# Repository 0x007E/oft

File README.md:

# `OFT` - Optical Fibre Transceiver

The `OFT` project is based on a fibre optic transmitter an receiver ([FB104](#additional-information)). The transmitter is based on a high-output medium-speed infrared LED while the transceiver is built on a high-sensitivity NPN phototransistor. Both are housed in a connector-less style plastic fiber optic package. The transmitter has a typical peak wavelength of `930nm`. The bandwith of the receiver is between `400nm` to `1100nm`. The maximum photosensitivity is around `870nm`. The receiver and transmitter is connected with an `RX` and `TX` LED over a `NE555` timer circuit to indicate if a data transmission occurrs.

> Note that the `IF-D92` is suitable for digital data links at rates up to `20kbps`!

| Experience | Level |
|:------------|:-----:|
| Soldering   |  |
| Mechanical  |  |

# Downloads

| Type      | File               | Description              |
|:---------:|:------------------:|:-------------------------|
| Schematic | [pdf](https://github.com/0x007E/oft/releases/latest/download/schematic.pdf) / [cadlab](https://cadlab.io/project/29648/main/files) | Schematic files |
| Board | [pdf](https://github.com/0x007E/oft/releases/latest/download/pcb.pdf) / [cadlab](https://cadlab.io/project/29648/main/files) | Board file |
| Drill | [pdf](https://github.com/0x007E/oft/releases/latest/download/drill.pdf) | Drill file |
| BoM | [xlsx](https://github.com/0x007E/oft/releases/latest/download/bom.xlsx) / [html](https://github.com/0x007E/oft/releases/latest/download/ibom.html)          | Bill of Material as Excel/interactive HTML |
| PCB    | [zip](https://github.com/0x007E/oft/releases/latest/download/kicad.zip) / [tar](https://github.com/0x007E/oft/releases/latest/download/kicad.tar.gz)    | KiCAD/Gerber/BoM/Drill files       |
| Mechanical | [zip](https://github.com/0x007E/oft/releases/latest/download/freecad.zip) / [tar](https://github.com/0x007E/oft/releases/latest/download/freecad.tar.gz) | FreeCAD/Housing and PCB (STEP/STL) files     |

# Hardware

There are two parts of the hardware. The pcb and the housing of the `OFT`. The pcb is created with [KiCAD](#additional-information) and the housing with `FreeCAD`. All files are built with `github actions` so that they are ready for a production environment. The housing is printed with a 3D-printer (`Dremel 3D40`).

## PCB

The circuit board is populated on both sides (Top, Bottom). The best way for soldering the `SMD` components is within a vapor phase soldering system and for the `THT` components with a standard soldering system.

### Top Layer

### Bottom Layer

## Mechanical

The housing has a tolerance of `0.2mm` on each side of the case. So the pcb should fit perfectly in the housing. The tolerance can be modified with `FreeCAD` in the `Parameter` Spreadsheet.

### Assembled

#### Exploded

# Connection/Setup

The `OFT` is powerd with `5V`. The `RX` pin serves as an output and stores the received data at the output so that it can be read by the device. The `TX` pin servs as an input and sends the received data at the input over the fibre channel. The levels of both pins are `LOW = 0V` and `HIGH = 5V`.

``` bash
#
#                                      +----------------+      +---------------------+
#                                      |    U       +---+---+  |                     |
#                                      |    S       |  USB  |--+ +-----------------+ |
#                                      |    B       +---+---+  | | TeraTerm        | |
#              +-------------+         |    /           |      | | ~~~~~~~~        | |
#              |      O      |         |    U           |      | | ~~~~~           | |
#            +--+--+  F   +--+--+   +--+--+ A           |      | | ~~~~~~~~~~~~    | |
#      L +---+ ORX |  T   | VCC +---+ VCC | R           |      | |                 | |
#      O |   +--+--+      | GND +---+ GND | T  +-+      |      | +-----------------+ |
#      O |      |         +-----+   +-----+   / /       |      |                     |
#      P |   +--+--+      | RXD +---+ RXD | +-+-+-+-----+      | Computer            |
#      B +---+ OTX |      | TXD +---+ TXD | | 5V  | 3V3 |      |                     |
#      A     +--+--+      +--+--+   +--+--+ +-----+-----+      +---------------------+
#      C       |             |
#      K       +-------------+                                            
#
```

> The maximum baudrate should be about `~19200bps`!

# Additional Information

| Type       | Link                                                   | Description                            |
|:----------:|:------------------------------------------------------:|:---------------------------------------|
| IF-E10     | [pdf](https://i-fiberoptics.com/pdf/if-e10.pdf)        | Optical fibre receiver and transmitter |
| NE555      | [pdf](https://www.ti.com/lit/ds/symlink/se555.pdf)     | Universal timer and oscillator         |
| KiCAD      | [web](https://www.kicad.org/)                          | KiCAD project page                     |
| FreeCAD    | [web](https://www.freecad.org/)                        | FreeCAD project page                   |

---

R. GAECHTER

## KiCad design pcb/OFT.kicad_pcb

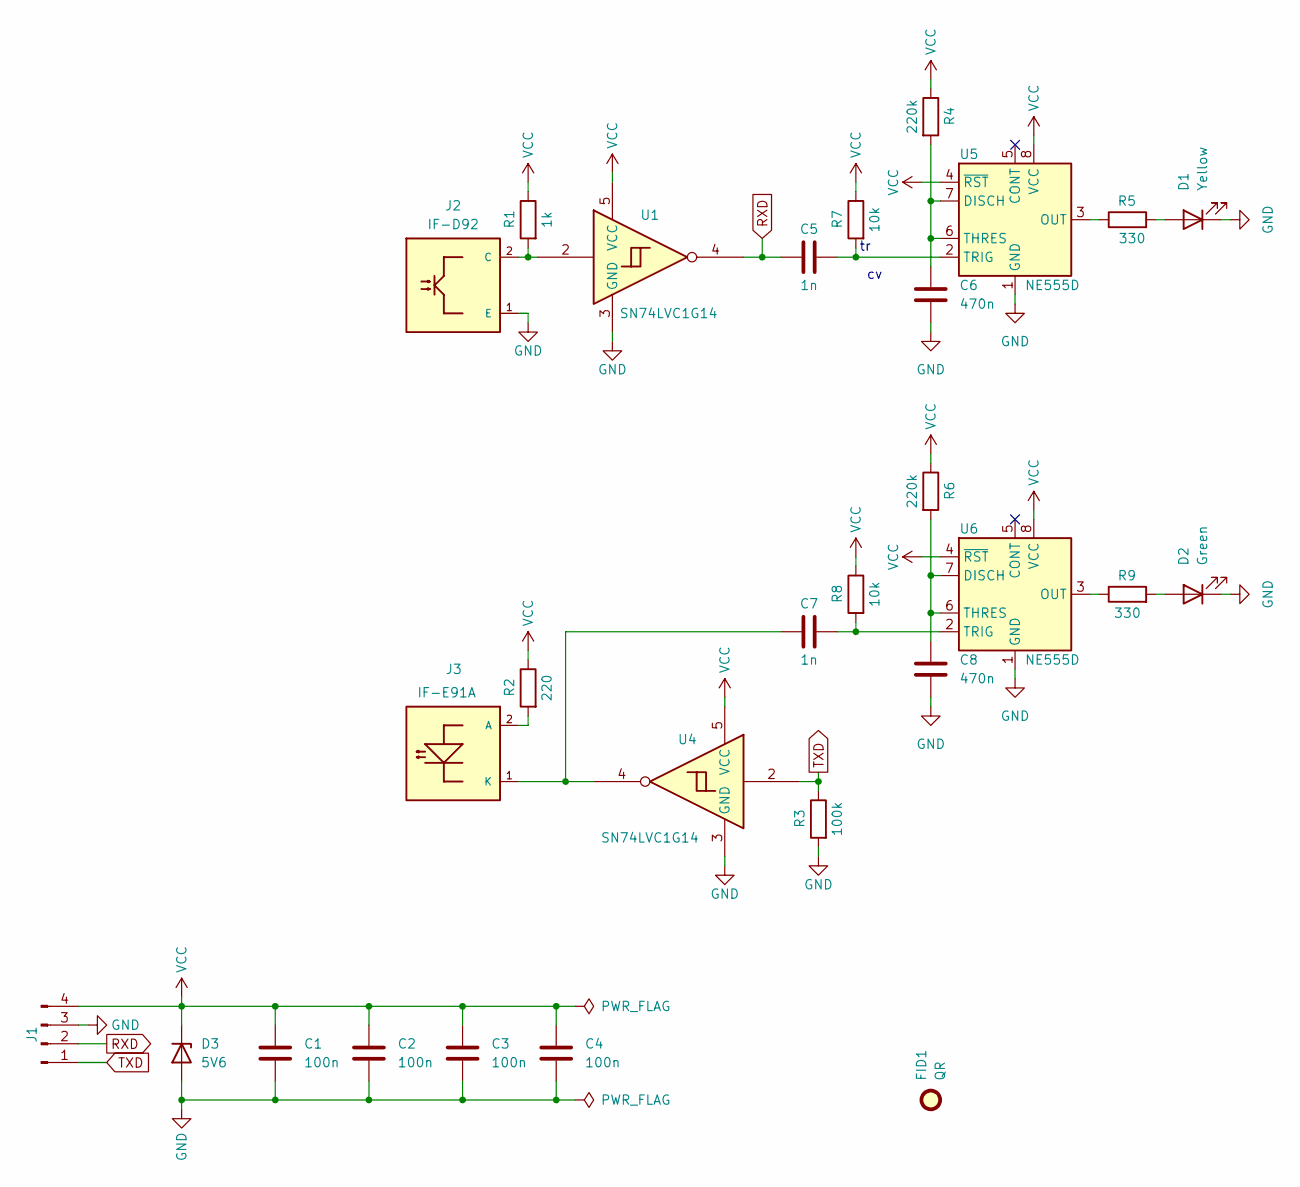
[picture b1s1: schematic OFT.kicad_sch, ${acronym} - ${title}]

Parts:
C1, C2, C3, C4: 100n; C_1206_3216Metric
C5, C7: 1n; C_1206_3216Metric
C6, C8: 470n; C_1206_3216Metric
D1: Yellow; LED_D3.0mm
D2: Green; LED_D3.0mm
D3: 5V6; D_MiniMELF
FID1: QR; QR_0x007e_very_small
J1: Conn_01x04_Pin; PinHeader_1x04_P2.54mm_Horizontal
J2: IF-D92
J3: IF-E91A
R1: 1k; R_1206_3216Metric
R2: 220; R_1206_3216Metric
R3: 100k; R_1206_3216Metric
R4, R6: 220k; R_1206_3216Metric
R5, R9: 330; R_1206_3216Metric
R7, R8: 10k; R_1206_3216Metric
U1, U4: SN74LVC1G14; SOT-353_SC-70-5
U5, U6: NE555D; SOIC-8_3.9x4.9mm_P1.27mm

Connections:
GND: C1.2, C2.2, C3.2, C4.2, C6.2, C8.2, D1.1 (K), D2.1 (K), D3.2 (A), J1.3, J2.1 (E), R3.2, U1.3 (GND), U4.3 (GND), U5.1 (GND), U6.1 (GND)
unnamed: D1.2 (A), R5.2
unnamed: D2.2 (A), R9.2
unnamed: J2.2 (C), R1.2, U1.2
unnamed: J3.2 (A), R2.2
unnamed: C7.1, J3.1 (K), U4.4
unnamed: C6.1, R4.2, U5.6 (THRES), U5.7 (DISCH)
unnamed: R5.1, U5.3 (OUT)
unnamed: C5.2, R7.2, U5.2 (TRIG)
unnamed: C8.1, R6.2, U6.6 (THRES), U6.7 (DISCH)
unnamed: R9.1, U6.3 (OUT)
unnamed: C7.2, R8.2, U6.2 (TRIG)
RXD: C5.1, J1.2, U1.4
TXD: J1.1, R3.1, U4.2
VCC: C1.1, C2.1, C3.1, C4.1, D3.1 (K), J1.4, R1.1, R2.1, R4.1, R6.1, R7.1, R8.1, U1.5 (VCC), U4.5 (VCC), U5.4 (~RST), U5.8 (VCC), U6.4 (~RST), U6.8 (VCC)

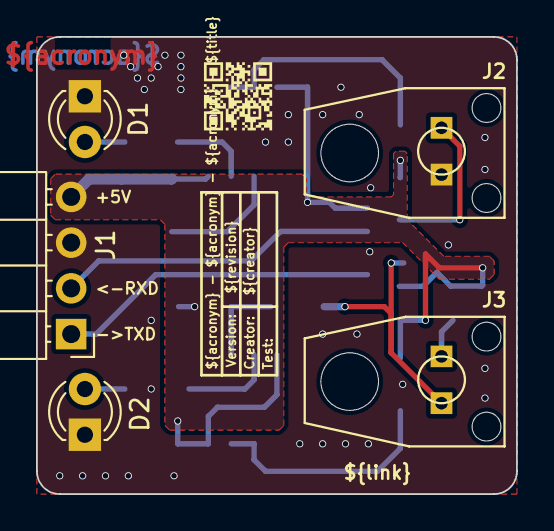
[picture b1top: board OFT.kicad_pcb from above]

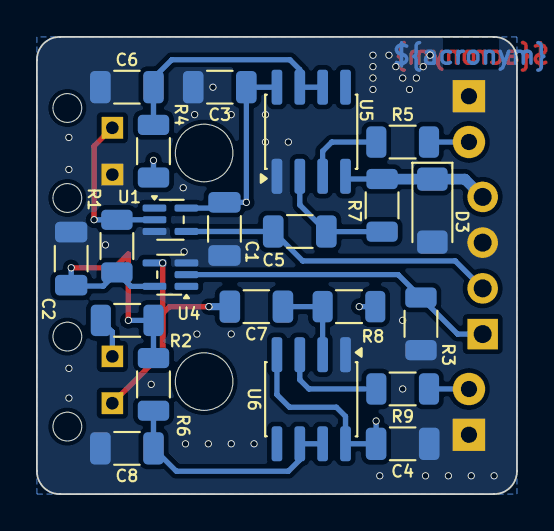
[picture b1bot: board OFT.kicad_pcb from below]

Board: 2 copper layers, 26.7 x 25.4 mm, 28 parts (22 on the bottom side), 15 nets.

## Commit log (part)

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2025-10-05 Add README.md
2025-10-05 Add build pipeline
2025-10-05 Adapt filter for drc warning
2025-10-05 Remove TechDraw
2025-10-05 Add release pipeline
2025-10-06 Change partlist vendors
2025-10-11 Add social image
2026-02-02 Fix wrong vendor id
2026-02-02 Add value to BoM

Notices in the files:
README.md:
License CC By-NC-SA
parts and their libraries:
license: CC BY-NC-SA 4.0
